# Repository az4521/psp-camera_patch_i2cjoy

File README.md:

# camera_patch_i2cjoy

This plugin can add right analog stick support to the PSP, using a TI ADS111x ADC connected to the PSP's i2c bus.

Based on camera_patch_lite by Freakler and CtrlHook from [Op-ditto](https://github.com/Operation-DITTO/ctrlHook)

the custom PCBs can be ordered from oshpark if you would like

https://oshpark.com/shared_projects/hx9D8oWi

I recommmend a flex pcb, because it's much thinner. the BOM is a single 0.1uf 0402 capacitor, and a TI ADS1115IDGS

#### Installation:
Copy the .prx & .ini files to your seplugins folder and add "ms0:/seplugins/camera_patch_i2joy.prx 1" to the game.txt file.

#### Notes:
This does not involve actual game patching but only shortcuts the already build-in camera controls of those games to the analog stick. Depending on the game this will work differently good or bad! Like sometimes there might be a small delay or you'll only be able to look left or right, but thats all game depending and better than nothing imo. Also if a game uses a trigger button + the left analog stick for camera movement you obviously won't be able to walk and move the camera at the same time for example.

Also some games are disabled by default in the .ini file due to the native patches by TheFlow. Use those plugins instead!

#### Demo: 
https://www.youtube.com/watch?v=mcaOkqbq82c

#### The following Games are supported currently:
```
.hack//link.
007 - From Russia with love
50Cent BulletProof G-Unit Edition
Aliens vs. Predator Requiem
Ape Escape: On the Loose
Assassins Creed: Bloodlines (disabled by default)
Avatar The Game
Ben 10 Aien Force Vilgax Attacks
Ben 10 Ultimate Alien Cosmic Destruction
Crisis Core: Final Fantasy VII
Coded Arms
Dantes Inferno (dodge with stick)
Daxter
Free Running
Ghostbusters: The Video Game
Gladiator Begins
God of War: Chains of Olympus (dodge with stick)
God of War: Ghost of Sparta (dodge with stick)
Grand Theft Auto Liberty City Stories (disabled by default)
Grand Theft Auto Vice City Stories (disabled by default)
Gun Showdown
Harvest Moon Hero of leaf valley
Indiana Jones and Staff of Kings
Iron Man
Iron Man 2
Jak & Daxter: The Lost Frontier
Manhunt 2
Marvel Ultimate Alliance
Marvel Ultimate Alliance 2
Medal of Honor Heroes
Medal of Honor Heroes 2
Metal Gear Solid - Peace Walker
Metal Gear Solid - Portable Ops
Miami Vice (strafe with stick)
Midnight Club LA Remix
Monster Hunter Freedom
Monster Hunter Freedom 2
Monster Hunter Freedom Unite
Monster Hunter Portable
Monster Hunter Portable 2nd
Monster Hunter Portable 3rd
Motorstorm Arctic Edge
Obscure: The Aftermath
Peter Jackson's King Kong
Pirates of the Caribbean - Dead man's chest
Prince of Persia - Revelations
Prince of Persia - Rival Swords
Ratatouille
Ratchet & Clank Size Matters
Rengoku: The Tower of Purgatory
Rengoku II: The Stairway to Heaven
Resistance Retribution (disabled by default)
Secret Agent Clank
Silent Hill: Shattered Memories
Skate Park City
Spiderman 2
Spiderman 3
Spinout
Splinter Cell Essentials (disabled by default)
Star Wars Battlefront 2
Star Wars Battlefront 2 Elite Squadron
Star Wars Battlefront 2 Renegade Squadron
Star Wars Lethal Alliance
Syphon Filter Dark Mirror
Syphon Filter Logan's Shadow
The Godfather
The Simpsons The Game
The Warriors
Tom Clancy's Rainbow Six Vegas
Tom Clancy's Ghost Recon Advanced Warfighter 2
Tom Clancy's Ghost Recon Predator
The Legend Of Heroes: Trails in the Sky
The Legend Of Heroes: Trails in the Sky Second Chapter
Tomb Raider: Legends (disabled by default)
Tomb Raider: Anniversary (disabled by default)
Tony Hawk's Underground 2
Toy Story 3
Valkyria Chronicles 2
Valkyria Chronicles 3: Extra Edition
Vertigo
```

#### Currently not working Games:
```
- Call of Duty Roads to Victory
- Death Jr.
- Final Fantasy Type0
- Kingdom Hearts: Birth By Sleep
- The 3rd Birthday
- Super Monkey Ball Adventure
```

To add a game yourself just edit the camera_patch_lite.ini file with the TitleID and settings you want.

Have fun :)

*Thanks & Greetings to: Team Molecule, The_FloW, reprep*

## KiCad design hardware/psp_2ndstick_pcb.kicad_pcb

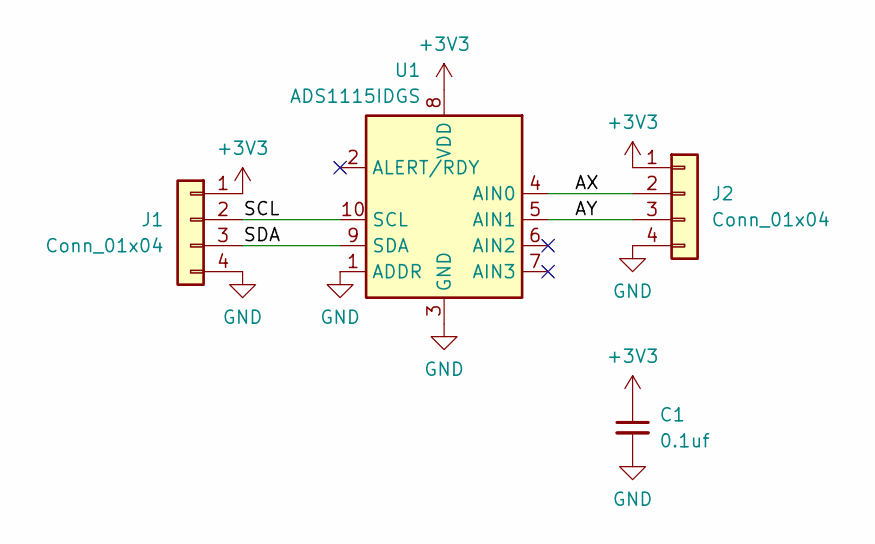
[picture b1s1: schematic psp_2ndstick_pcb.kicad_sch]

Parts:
C1: 0.1uf; C_0402_1005Metric_Pad0.74x0.62mm_HandSolder
J1, J2: Conn_01x04; PinHeader_1x04_P1.27mm_Vertical
U1: ADS1115IDGS; TSSOP-10_3x3mm_P0.5mm

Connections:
+3V3: C1.1, J1.1, J2.1, U1.8 (VDD)
/AX: J2.2, U1.4 (AIN0)
/AY: J2.3, U1.5 (AIN1)
/SCL: J1.2, U1.10 (SCL)
/SDA: J1.3, U1.9 (SDA)
GND: C1.2, J1.4, J2.4, U1.1 (ADDR), U1.3 (GND)

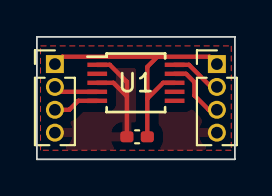
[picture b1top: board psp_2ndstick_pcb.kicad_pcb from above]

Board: 2 copper layers, 11.0 x 6.8 mm, 4 parts (0 on the bottom side), 6 nets.

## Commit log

2024-07-06 remove adrenaline checks, add i2c functions
2024-07-06 add pcb designs and pin locations for psp 1k and 2k
2024-07-07 this doesn't work at all
